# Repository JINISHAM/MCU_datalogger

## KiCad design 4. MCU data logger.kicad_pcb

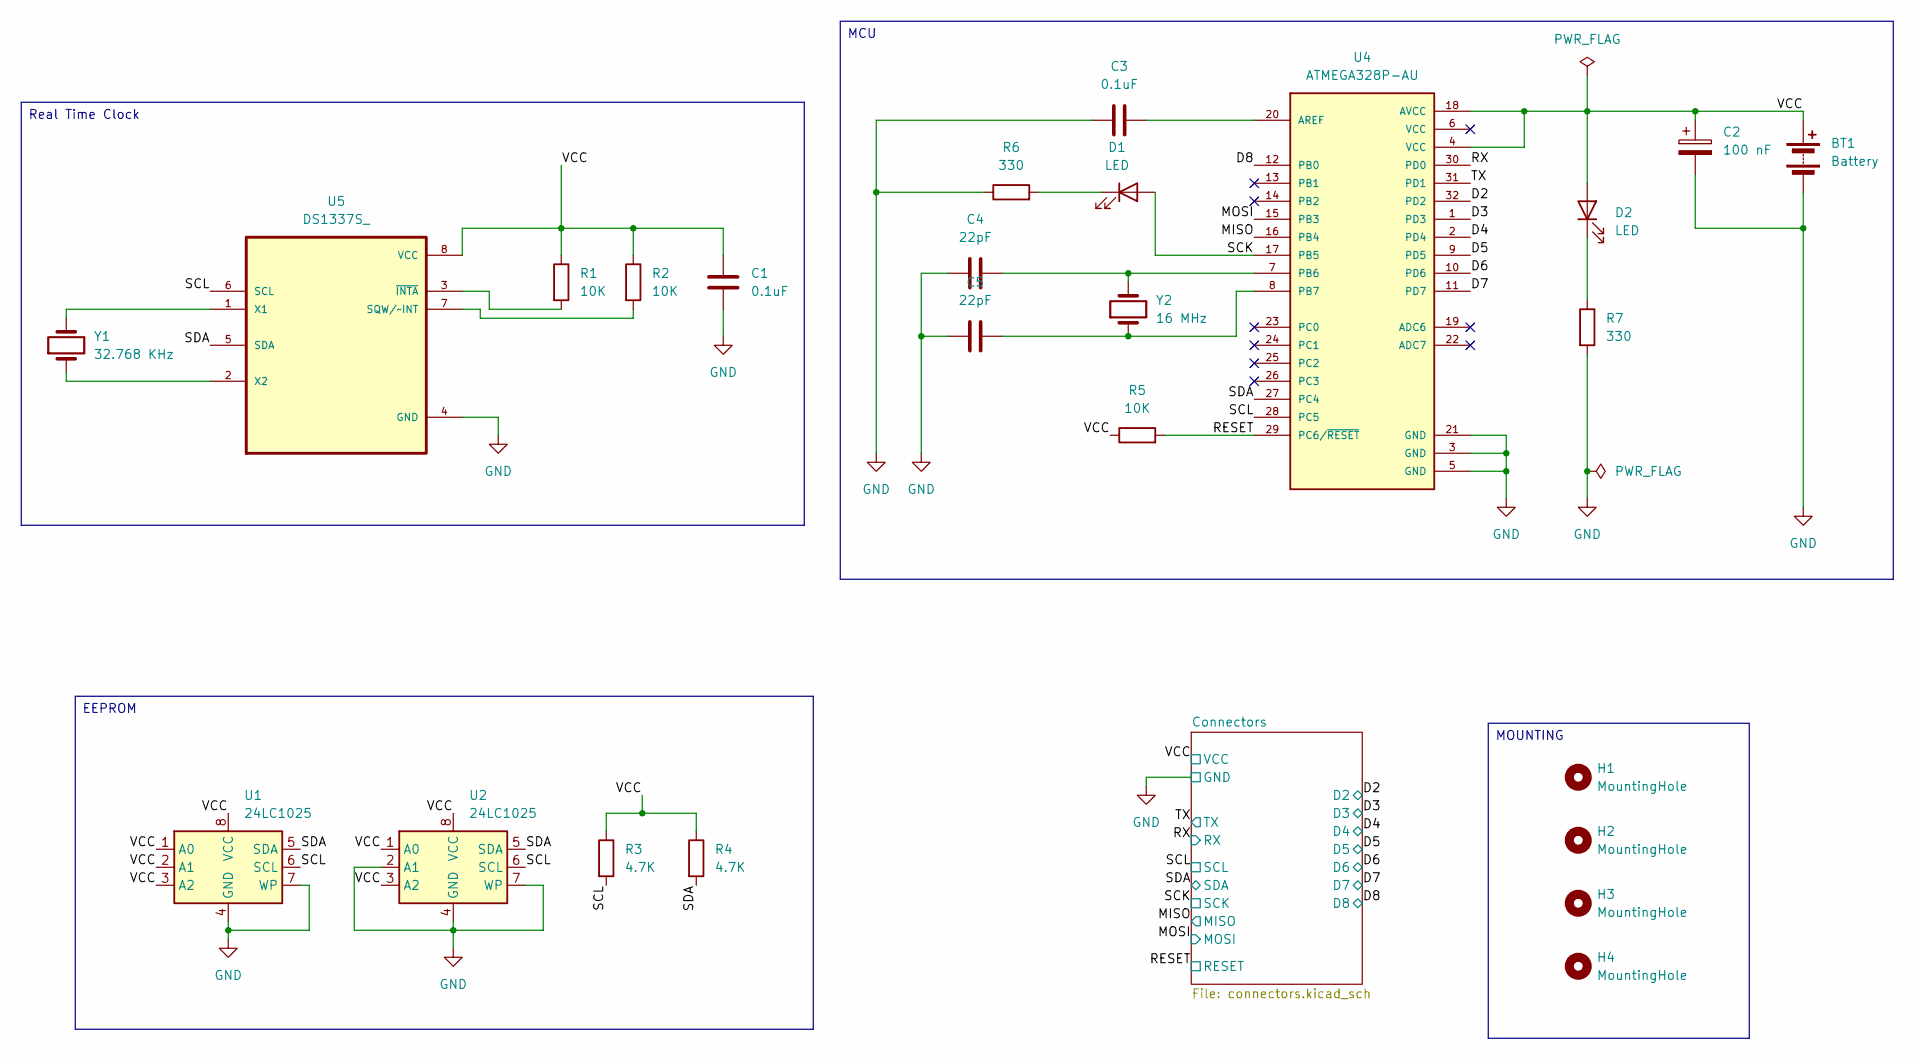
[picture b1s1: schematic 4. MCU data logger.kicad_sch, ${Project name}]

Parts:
BT1: Battery; PinHeader_1x02_P2.54mm_Vertical
C1, C3: 0.1uF; C_0805_2012Metric
C2: 100 nF; C_0805_2012Metric
C4, C5: 22pF; C_0805_2012Metric
D1, D2: LED; LED_0805_2012Metric
H1, H2, H3, H4: MountingHole; MountingHole_2.1mm
R1, R2, R5: 10K; R_0805_2012Metric
R3, R4: 4.7K; R_0805_2012Metric
R6, R7: 330; R_0805_2012Metric
U1, U2: 24LC1025; SOIC-8_5.3x5.3mm_P1.27mm
U4: ATMEGA328P-AU; QFP80P900X900X120-32N; PARTREV 8271A; DigiKey_Part_Number ATMEGA328P-AU-ND
U5: DS1337S_; SOIC127P600X175-8N
Y1: 32.768 KHz; Crystal_SMD_5032-2Pin_5.0x3.2mm_HandSoldering
Y2: 16 MHz; Crystal_SMD_5032-2Pin_5.0x3.2mm_HandSoldering

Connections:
/D2: U4.32 (PD2); also elsewhere on the board
/D3: U4.1 (PD3); also elsewhere on the board
/D4: U4.2 (PD4); also elsewhere on the board
/D5: U4.9 (PD5); also elsewhere on the board
/D6: U4.10 (PD6); also elsewhere on the board
/D7: U4.11 (PD7); also elsewhere on the board
/D8: U4.12 (PB0); also elsewhere on the board
/MISO: U4.16 (PB4); also elsewhere on the board
/MOSI: U4.15 (PB3); also elsewhere on the board
/RESET: R5.2, U4.29 (PC6/~RESET); also elsewhere on the board
/RX: U4.30 (PD0); also elsewhere on the board
/SCK: D1.2 (A), U4.17 (PB5); also elsewhere on the board
/SCL: R3.2, U1.6 (SCL), U2.6 (SCL), U4.28 (PC5), U5.6 (SCL); also elsewhere on the board
/SDA: R4.2, U1.5 (SDA), U2.5 (SDA), U4.27 (PC4), U5.5 (SDA); also elsewhere on the board
/TX: U4.31 (PD1); also elsewhere on the board
/VCC: BT1.1 (+), C1.1, C2.1, D2.2 (A), R1.1, R2.1, R3.1, R4.1, R5.1, U1.1 (A0), U1.2 (A1), U1.3 (A2), U1.8 (VCC), U2.1 (A0), U2.3 (A2), U2.8 (VCC), U4.4 (VCC), U4.18 (AVCC), U5.8 (VCC); also elsewhere on the board
GND: BT1.2 (-), C1.2, C2.2, C3.1, C4.1, C5.1, R6.1, R7.2, U1.4 (GND), U1.7 (WP), U2.2 (A1), U2.4 (GND), U2.7 (WP), U4.3 (GND), U4.5 (GND), U4.21 (GND), U5.4 (GND); also elsewhere on the board
unnamed: D1.1 (K), R6.2
unnamed: D2.1 (K), R7.1
unnamed: C3.2, U4.20 (AREF)
unnamed: C4.2, U4.7 (PB6), Y2.2
unnamed: C5.2, U4.8 (PB7), Y2.1
unnamed: R2.2, U5.7 (SQW/~INT)
unnamed: U5.1 (X1), Y1.2
unnamed: U5.2 (X2), Y1.1
unnamed: R1.2, U5.3 (~INTA)

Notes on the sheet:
Real Time Clock
MCU
MOUNTING
EEPROM

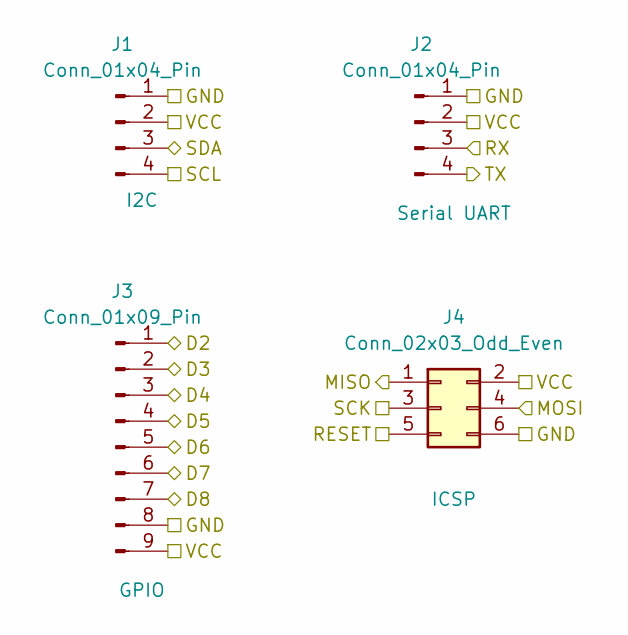
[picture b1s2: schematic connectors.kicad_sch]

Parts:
J1, J2: Conn_01x04_Pin; PinHeader_1x04_P2.54mm_Vertical
J3: Conn_01x09_Pin; PinHeader_1x09_P2.54mm_Vertical
J4: Conn_02x03_Odd_Even; PinHeader_2x03_P2.54mm_Vertical

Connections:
/D2: J3.1; also elsewhere on the board
/D3: J3.2; also elsewhere on the board
/D4: J3.3; also elsewhere on the board
/D5: J3.4; also elsewhere on the board
/D6: J3.5; also elsewhere on the board
/D7: J3.6; also elsewhere on the board
/D8: J3.7; also elsewhere on the board
/MISO: J4.1; also elsewhere on the board
/MOSI: J4.4; also elsewhere on the board
/RESET: J4.5; also elsewhere on the board
/RX: J2.3; also elsewhere on the board
/SCK: J4.3; also elsewhere on the board
/SCL: J1.4; also elsewhere on the board
/SDA: J1.3; also elsewhere on the board
/TX: J2.4; also elsewhere on the board
/VCC: J1.2, J2.2, J3.9, J4.2; also elsewhere on the board
GND: J1.1, J2.1, J3.8, J4.6; also elsewhere on the board

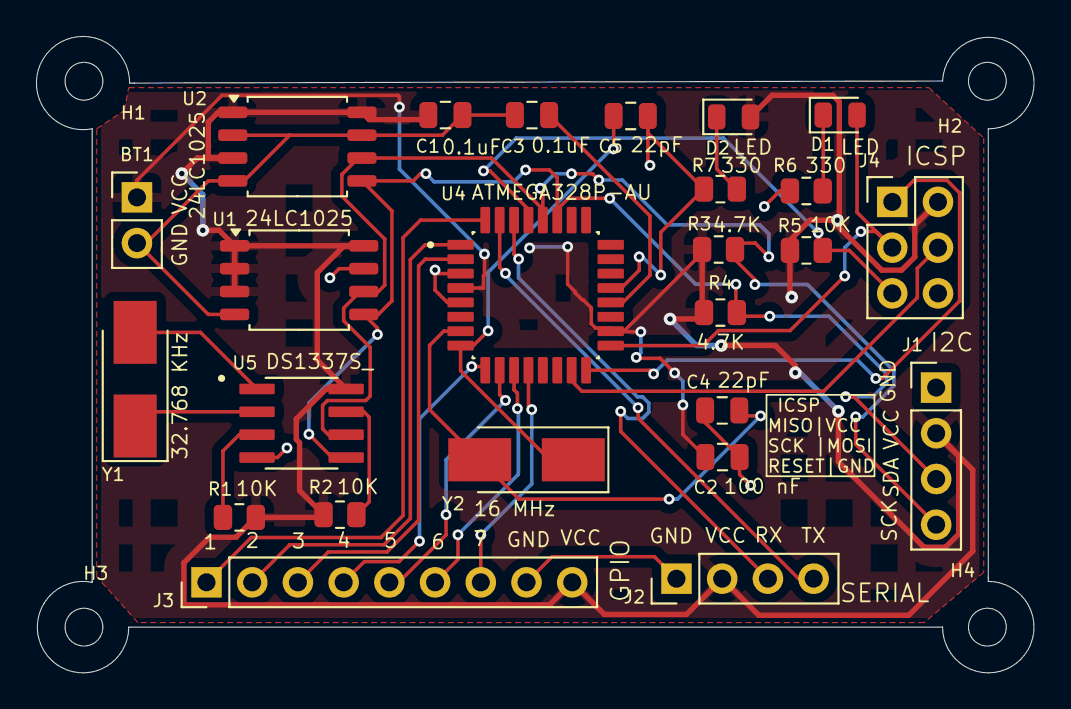
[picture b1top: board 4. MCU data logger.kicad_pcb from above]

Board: 2 copper layers, 55.4 x 35.4 mm, 29 parts (0 on the bottom side), 26 nets.

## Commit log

2025-05-28 First commit of new project
2025-05-28 Setup of eeschema for new project
2025-05-28 Symbols have been added
2025-05-28 Symbols values have been added
2025-05-28 Footprints associated
2025-05-29 wiring has been done
2025-05-29 nets have been added
2025-05-29 added comments
2025-06-06 pcb setup
2025-06-06 components placed
2025-06-28 Routing Completed
2025-07-06 Completed 2layer project
2025-07-06 Removed temporary .lck files from repository
2025-07-06 Fixed a defect
2025-07-07 Fixed defects in schematic
2025-07-07 Fixed defects in pcb
